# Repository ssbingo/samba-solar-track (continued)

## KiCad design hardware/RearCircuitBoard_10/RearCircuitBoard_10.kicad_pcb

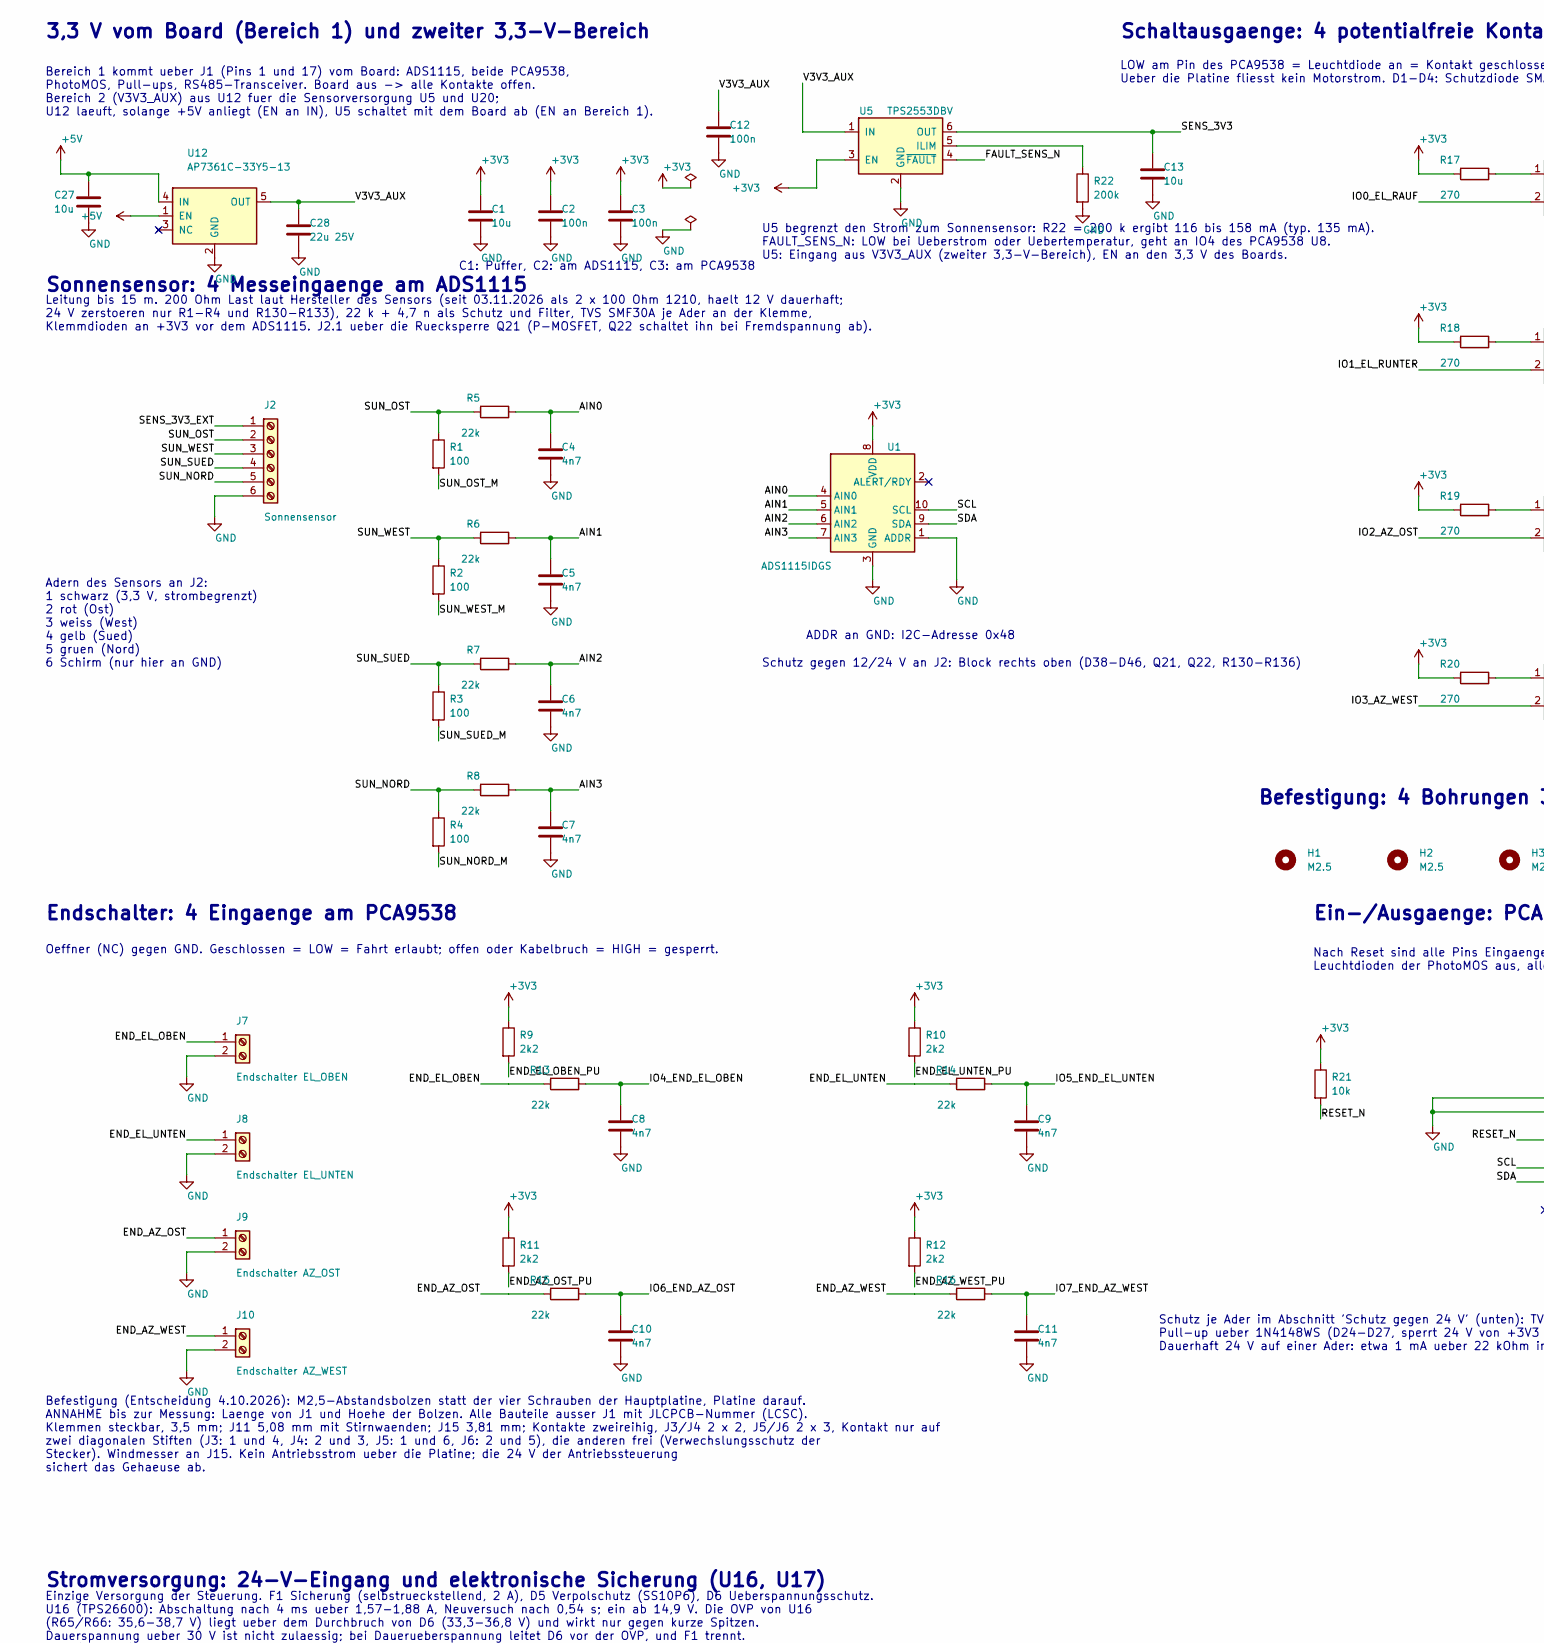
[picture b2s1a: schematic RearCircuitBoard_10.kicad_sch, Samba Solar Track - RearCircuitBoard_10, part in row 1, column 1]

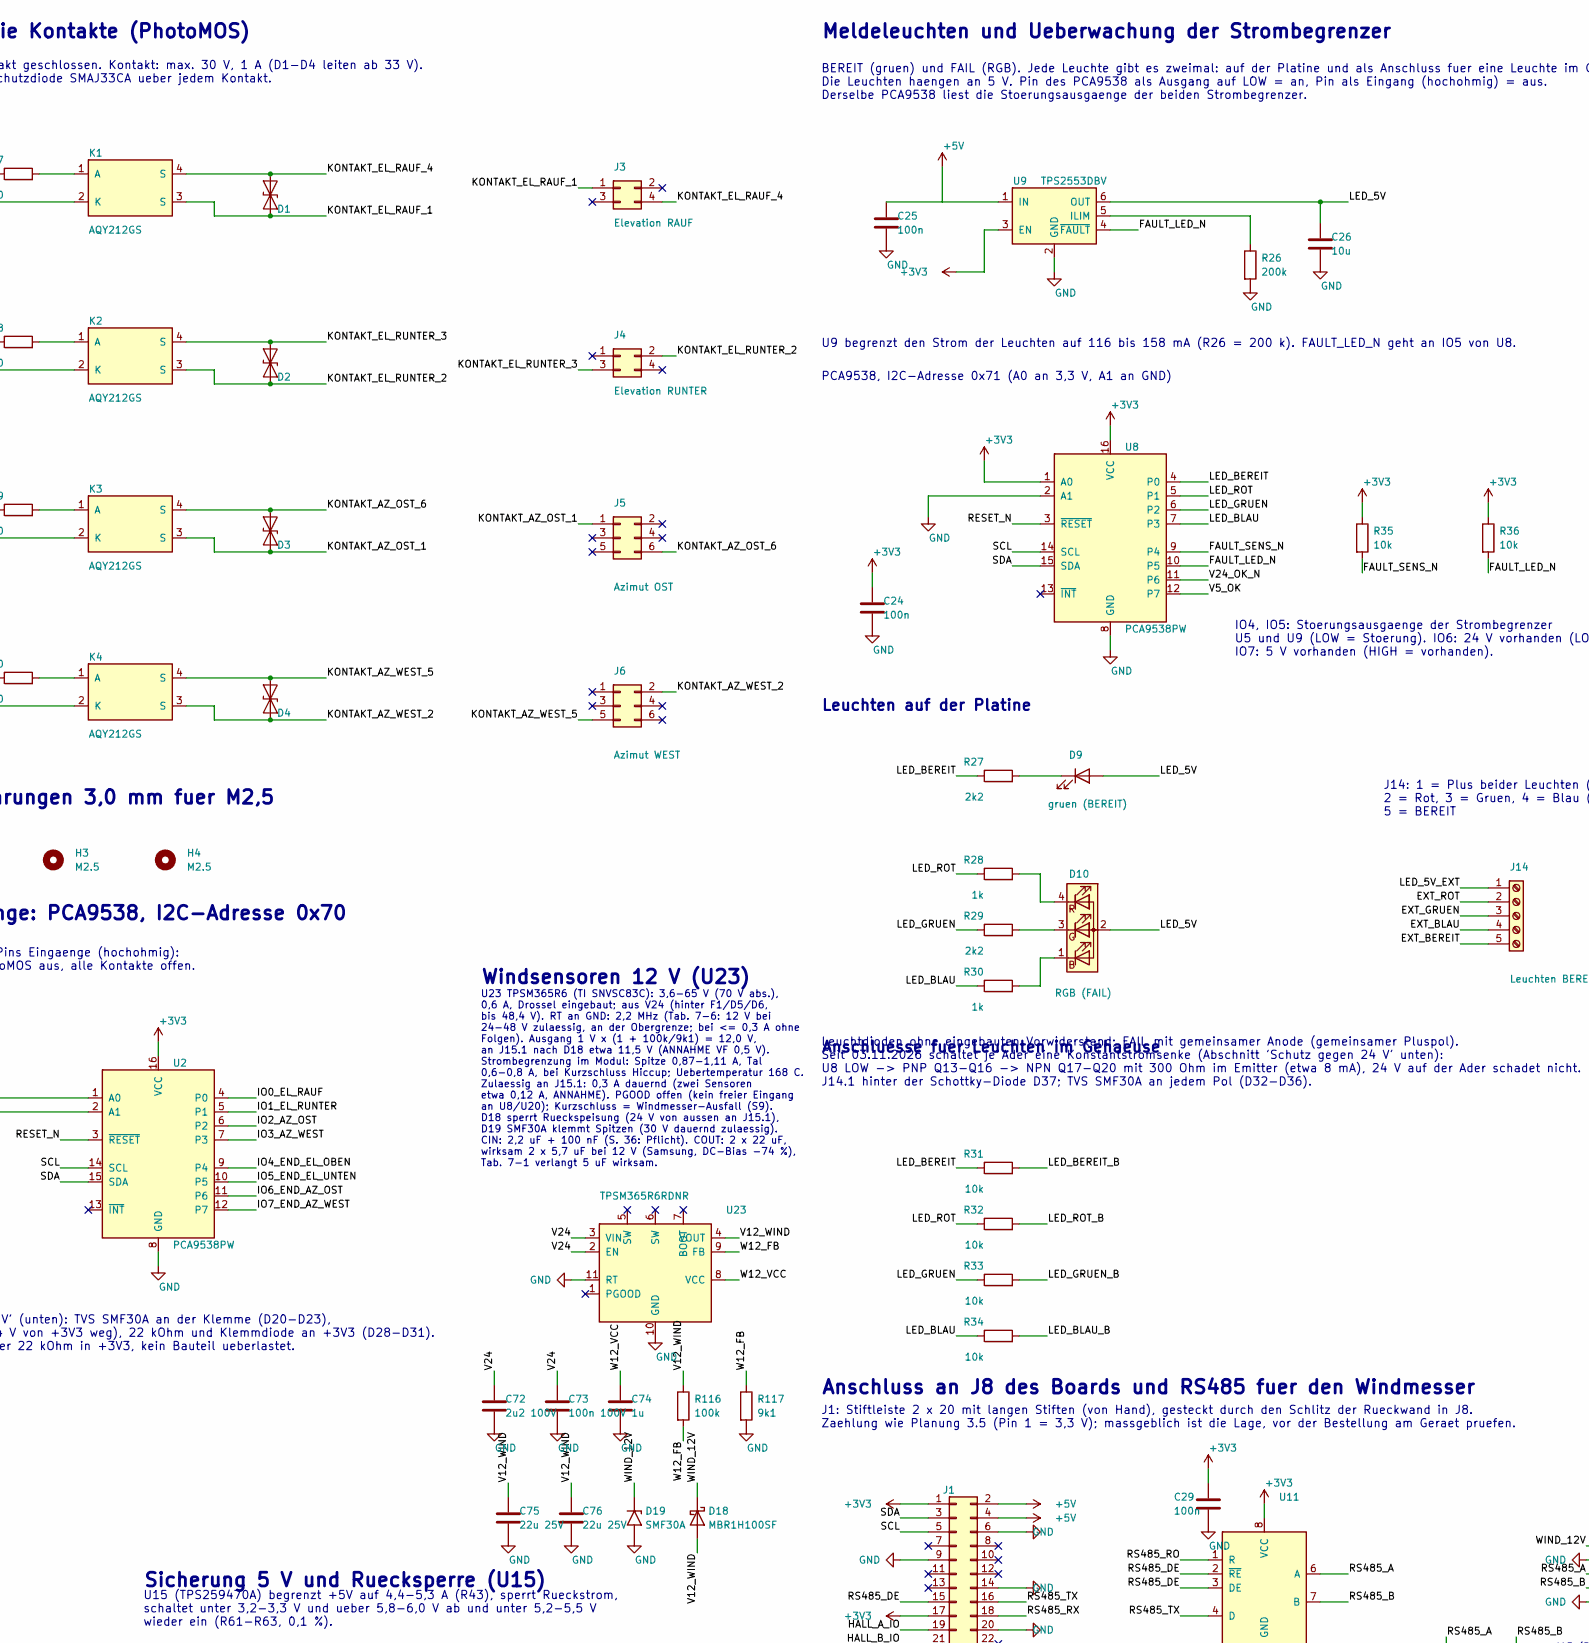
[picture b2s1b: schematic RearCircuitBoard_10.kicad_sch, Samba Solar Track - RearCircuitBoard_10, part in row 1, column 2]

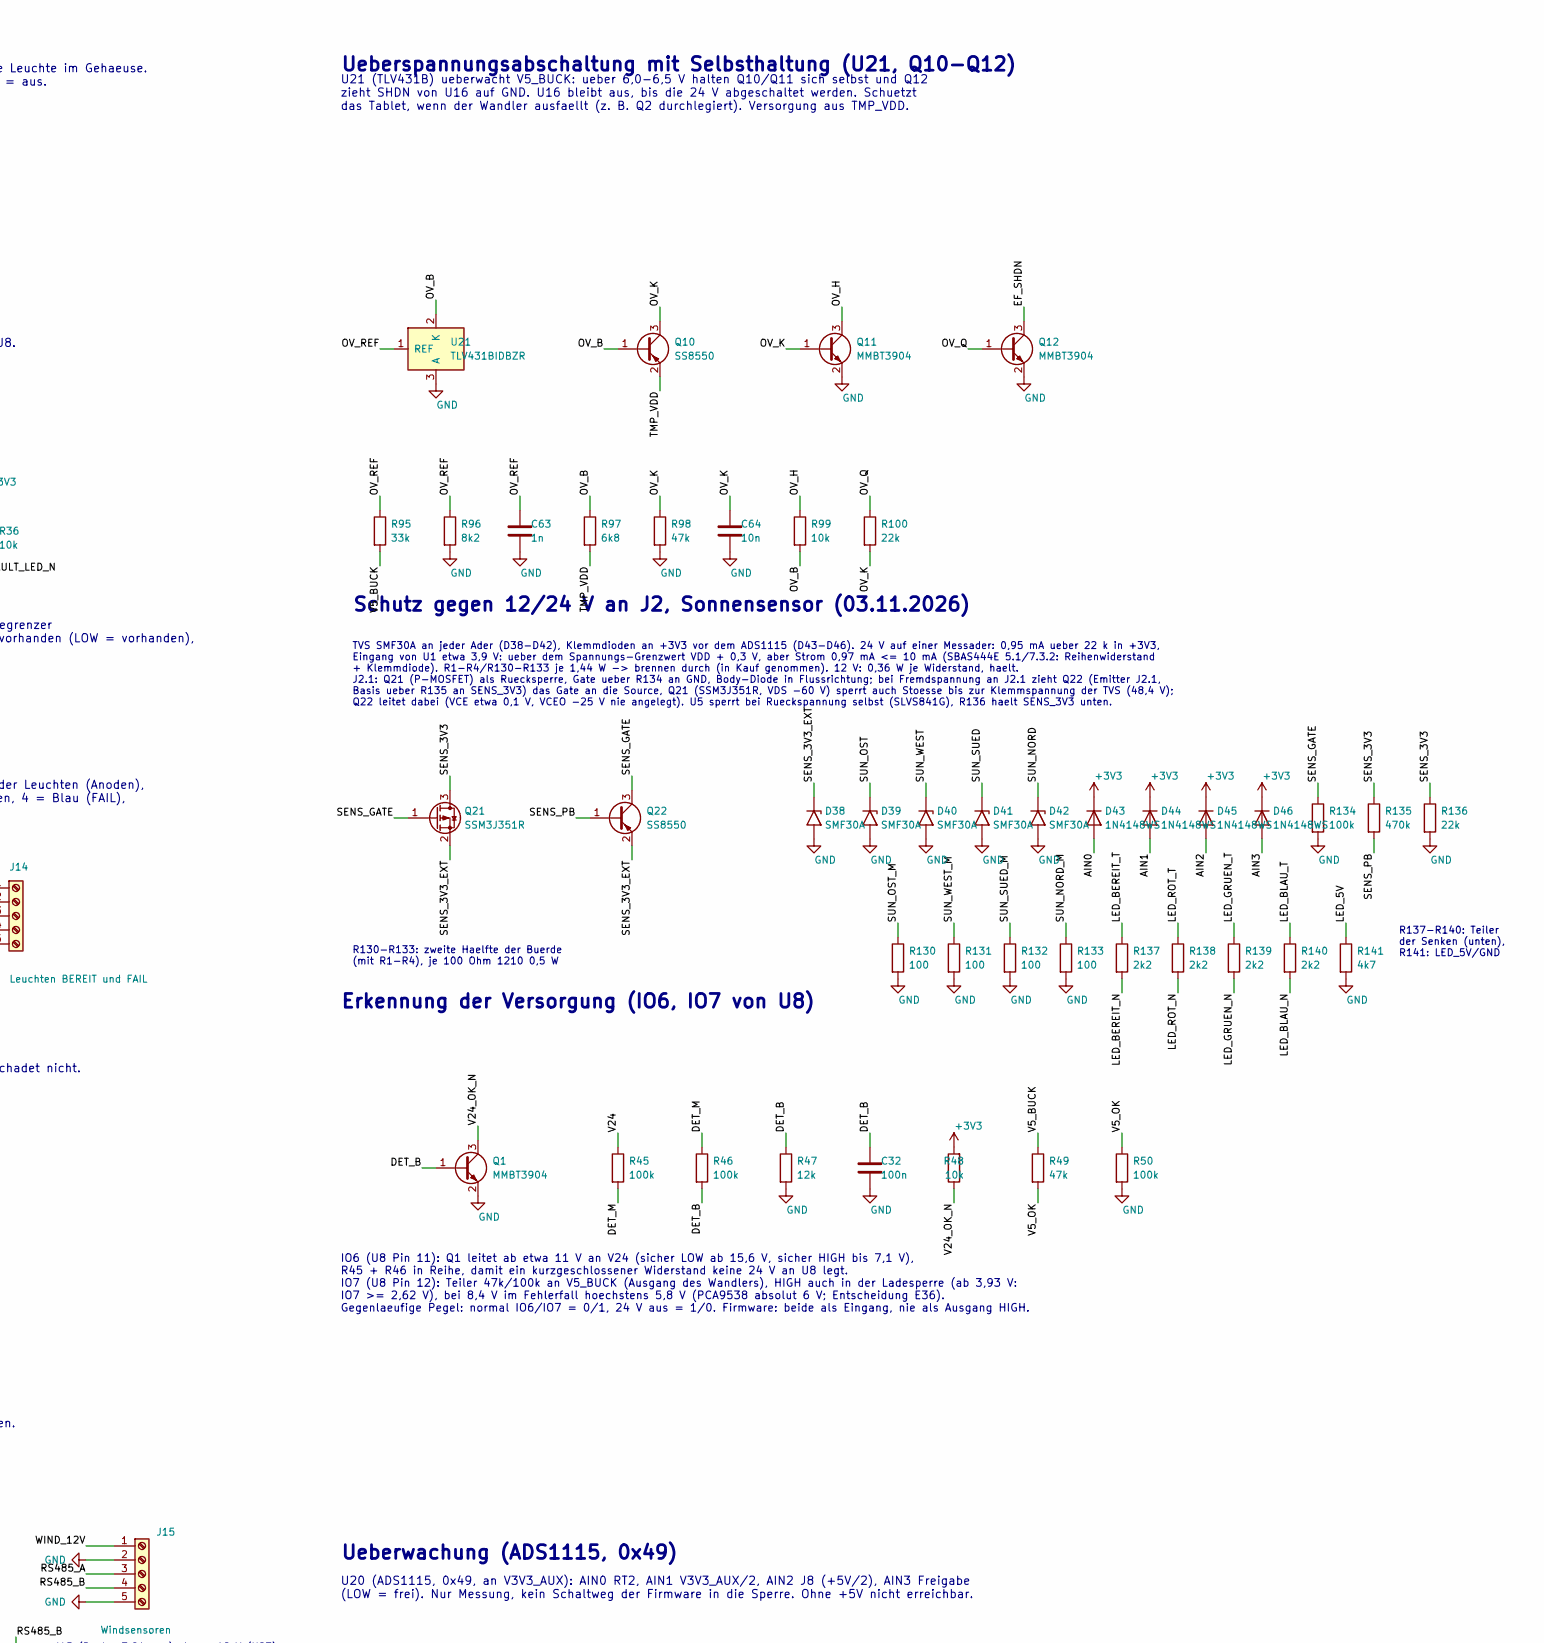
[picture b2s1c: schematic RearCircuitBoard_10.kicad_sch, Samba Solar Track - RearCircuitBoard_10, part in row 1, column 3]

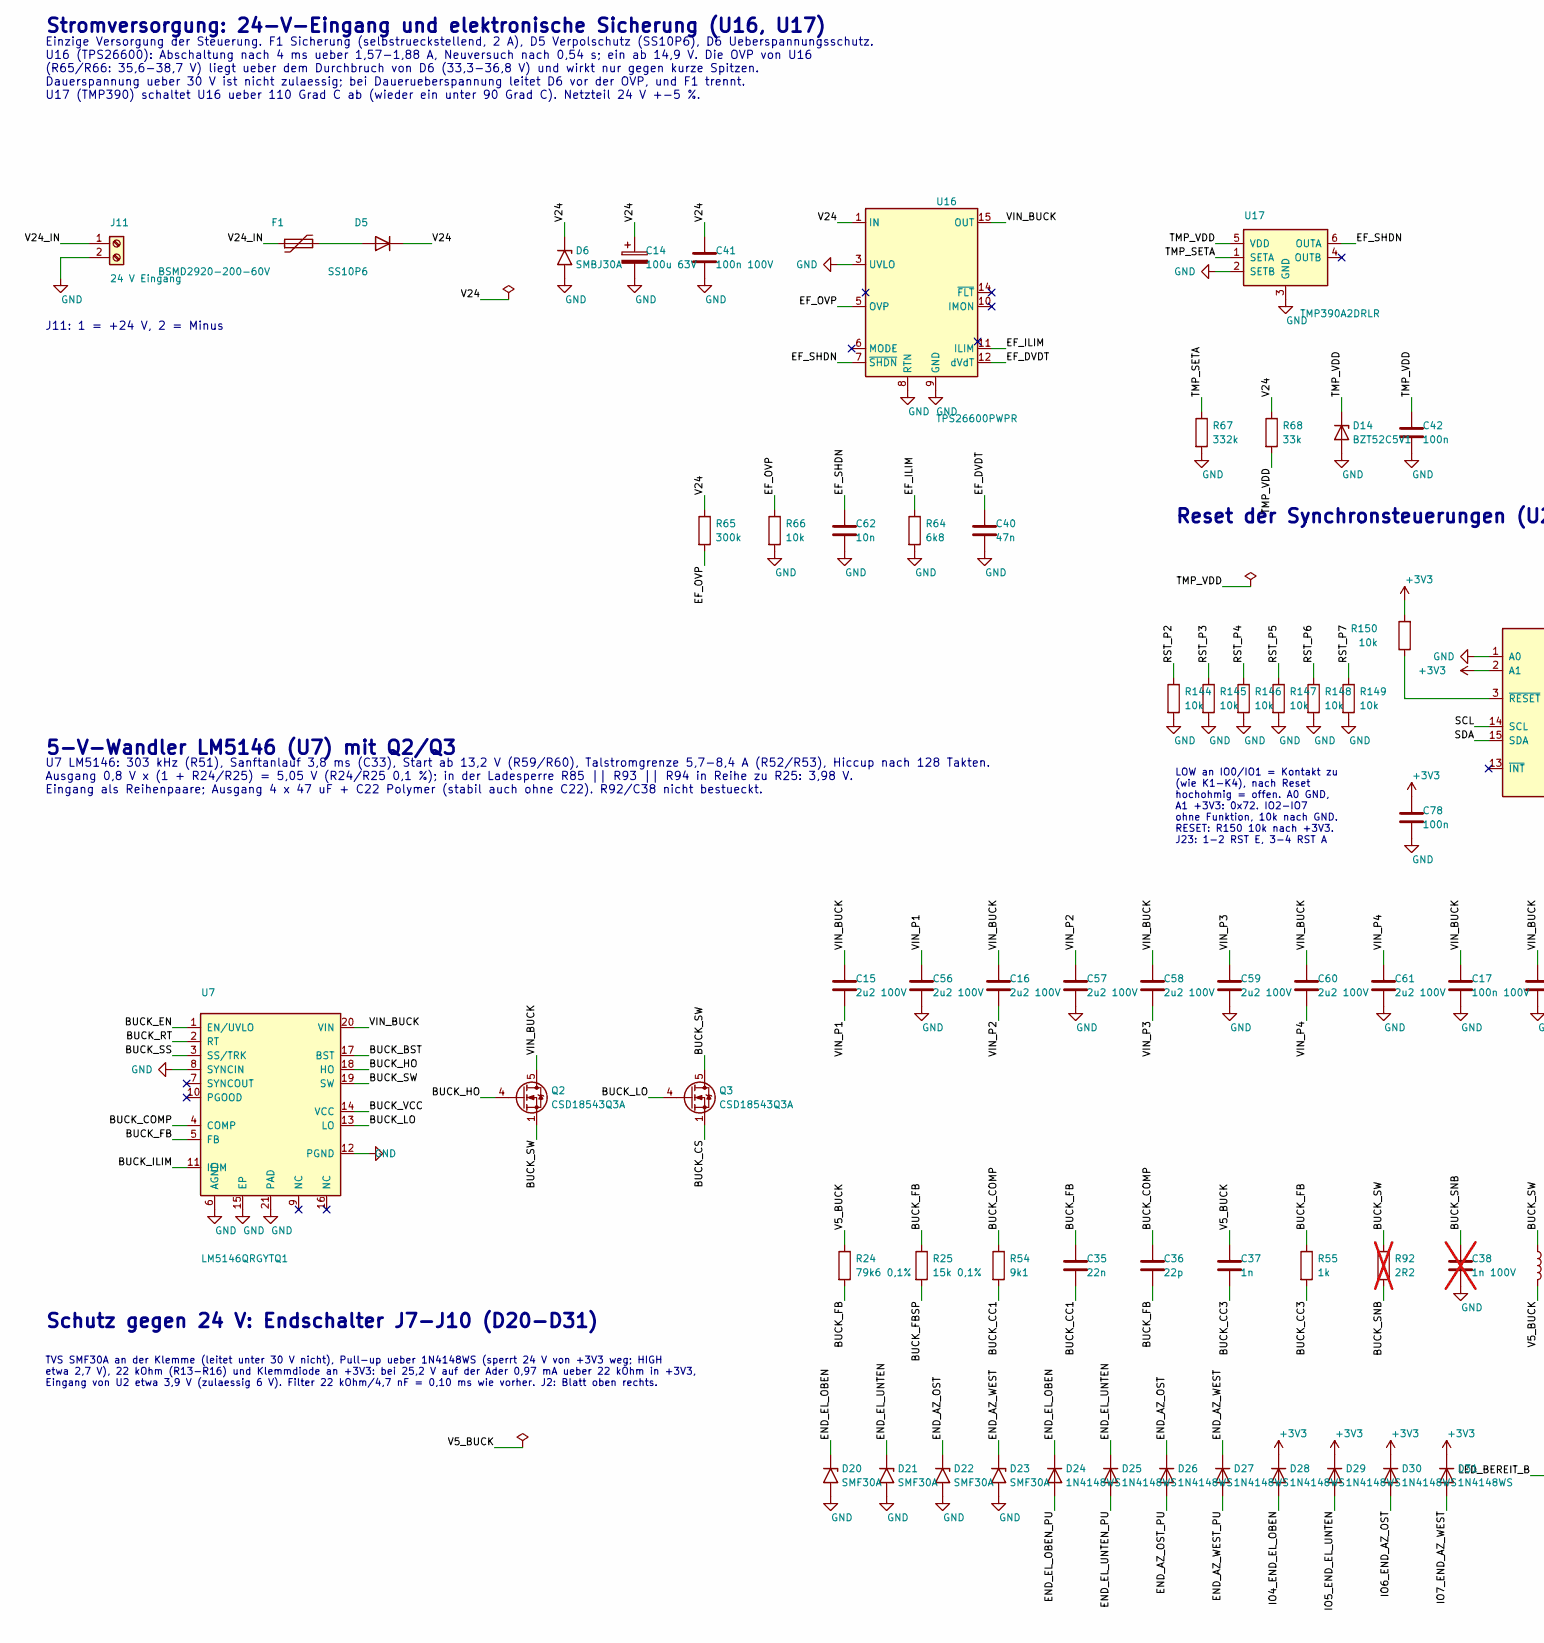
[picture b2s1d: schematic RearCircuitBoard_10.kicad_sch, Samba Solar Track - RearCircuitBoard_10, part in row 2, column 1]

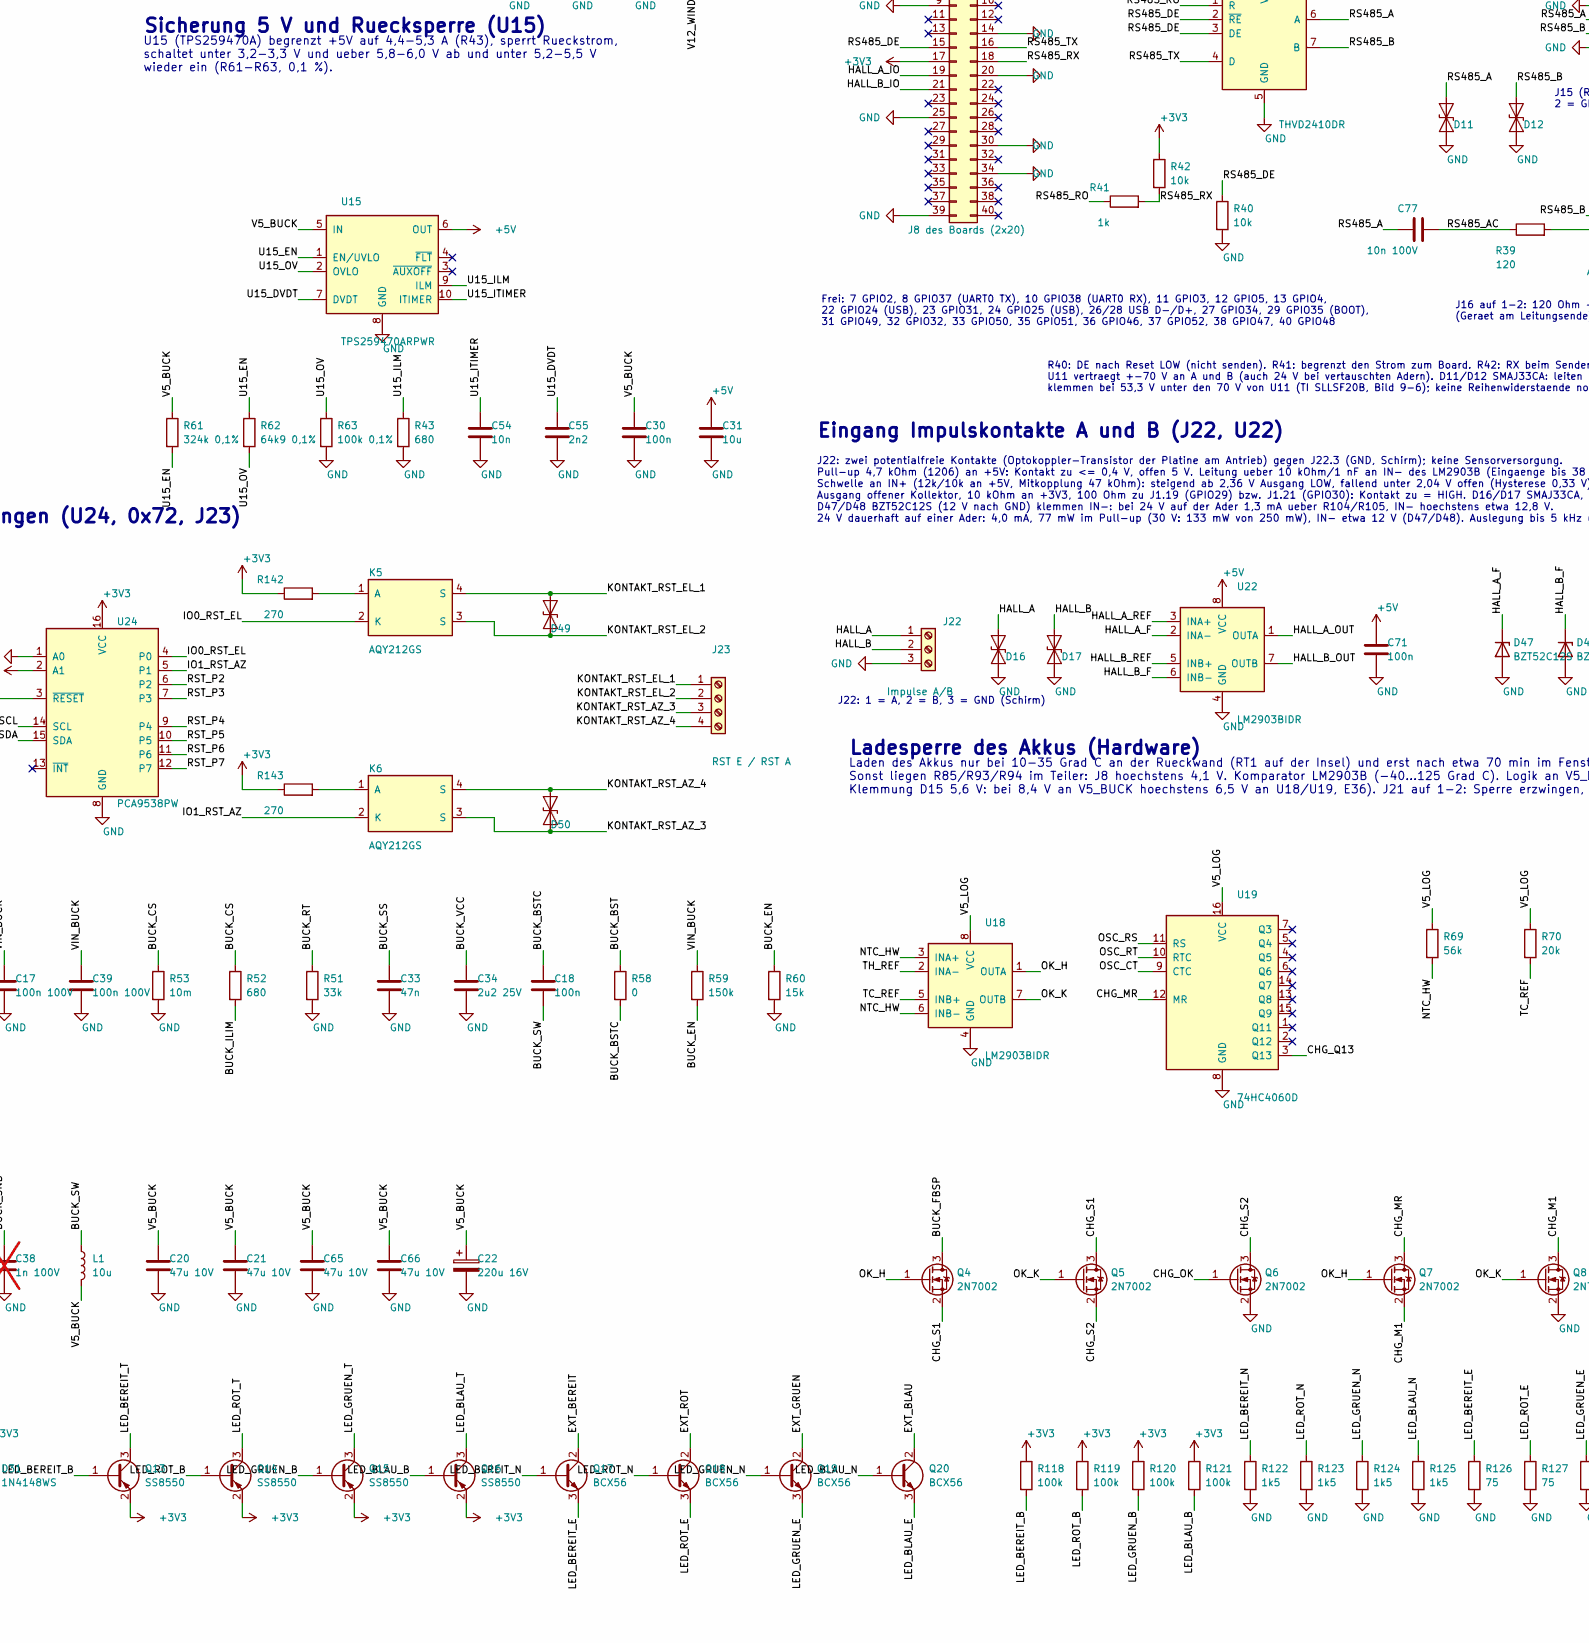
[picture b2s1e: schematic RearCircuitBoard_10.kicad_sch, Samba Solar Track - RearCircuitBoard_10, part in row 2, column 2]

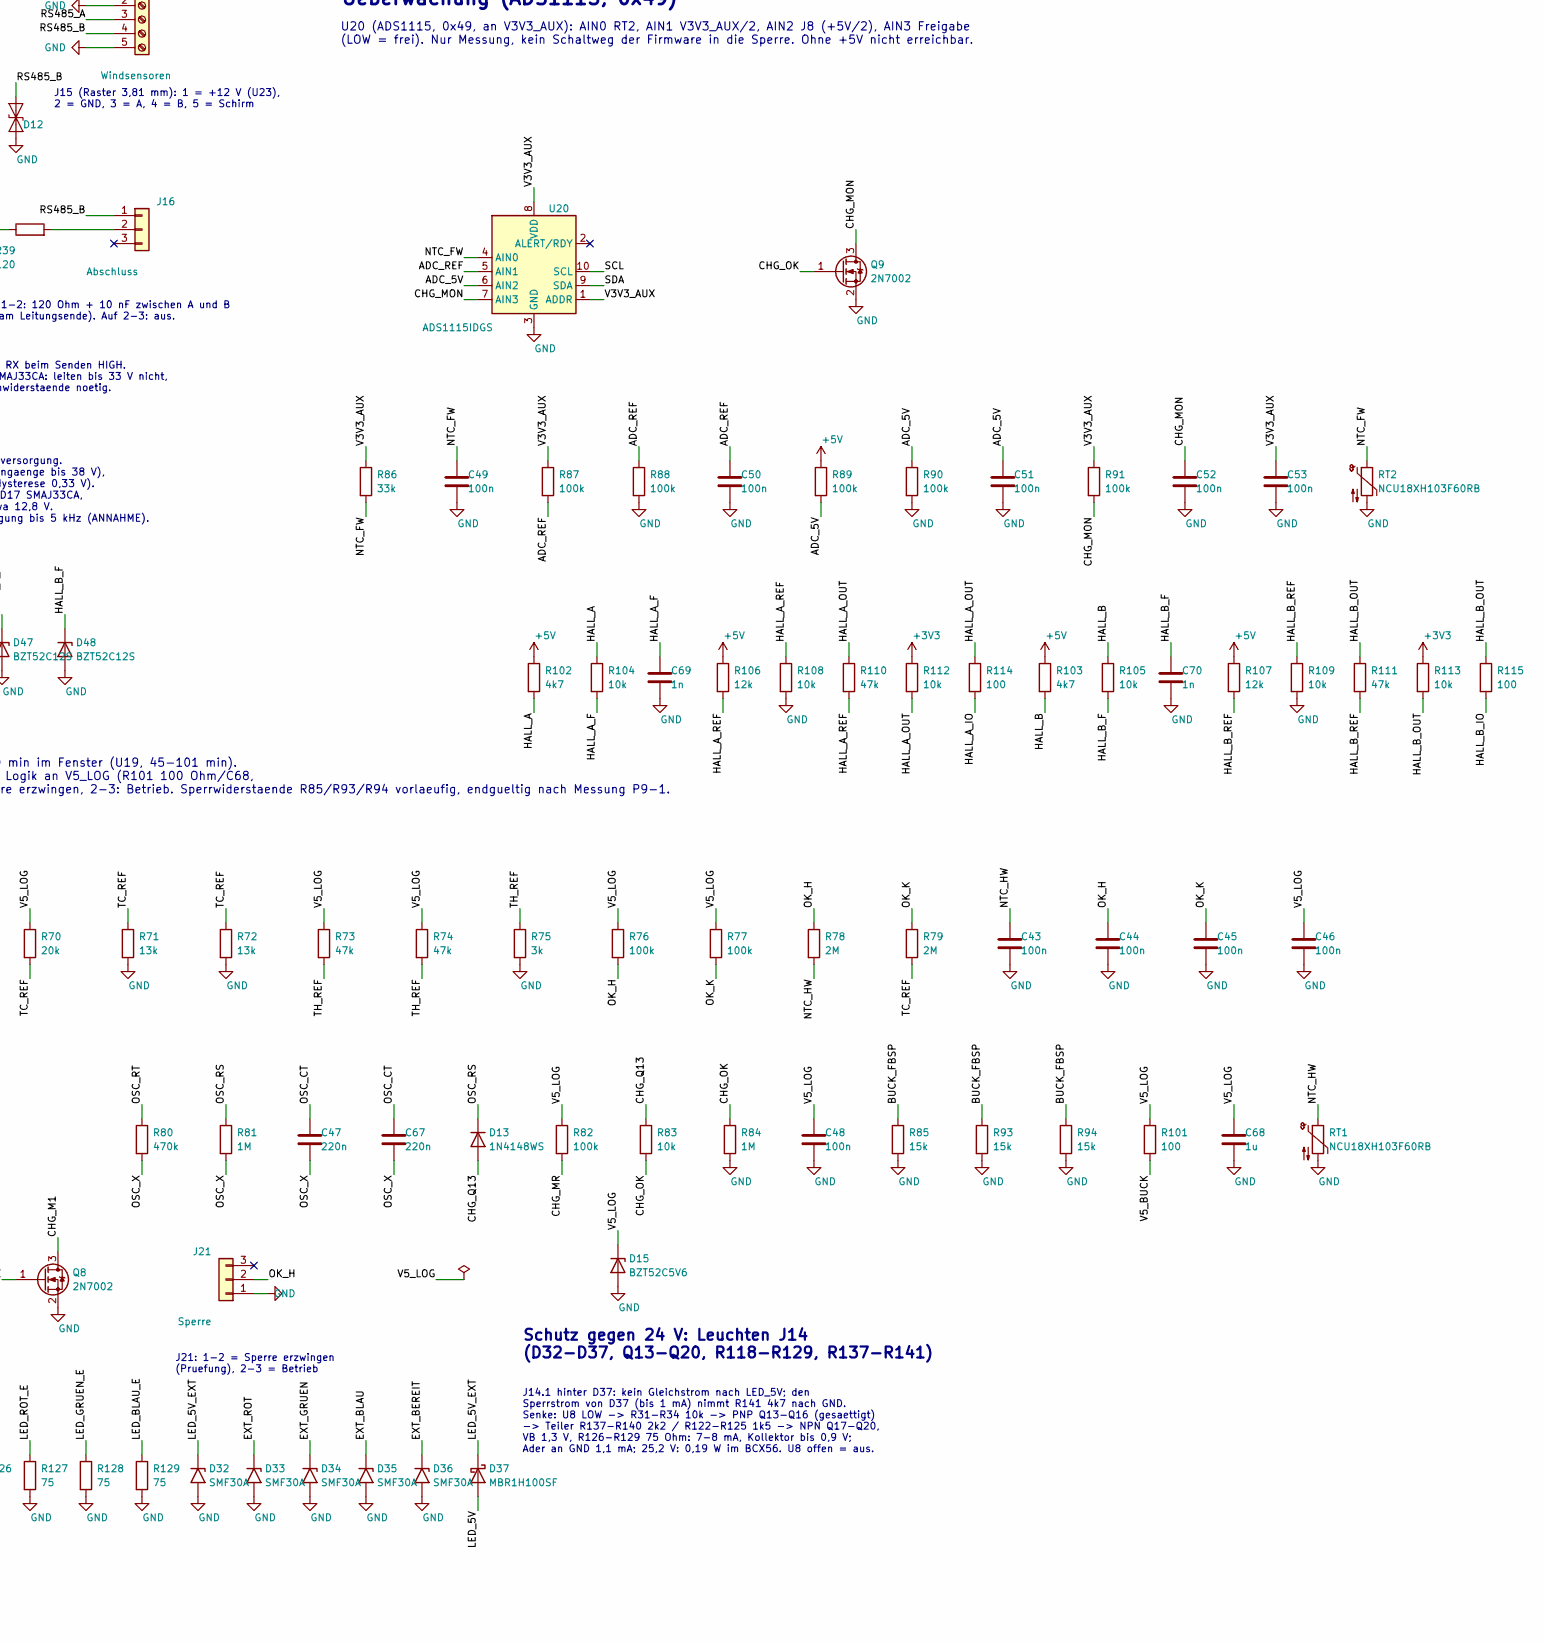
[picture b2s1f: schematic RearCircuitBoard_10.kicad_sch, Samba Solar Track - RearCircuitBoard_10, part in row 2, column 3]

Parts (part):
C1, C13, C26, C27: 10u; C_0603_1608Metric; LCSC C19702
C2, C3, C12, C18, C24, C25, C29, C30, C32, C42, C43, C44, C45, C46, C48, C49, C50, C51, C52, C53, C71, C78: 100n; C_0603_1608Metric; LCSC C14663
C4, C5, C6, C7, C8, C9, C10, C11: 4n7; C_0603_1608Metric; LCSC C53987
C14: 100u 63V; CP_Elec_8x10; LCSC C487384
C15, C16, C56, C57, C58, C59, C60, C61, C72: 2u2 100V; C_1206_3216Metric; LCSC C16195971
C17, C39, C41: 100n 100V; C_0805_2012Metric; LCSC C3011698
C20, C21, C65, C66: 47u 10V; C_1210_3225Metric; LCSC C7198516
C22: 220u 16V; CP_Elec_6.3x7.7; LCSC C709481
C28, C75, C76: 22u 25V; C_1206_3216Metric; LCSC C12891
C31: 10u; C_0603_1608Metric; LCSC C2959727
C33, C40: 47n; C_0603_1608Metric; LCSC C1622
C34: 2u2 25V; C_0805_2012Metric; LCSC C19110
C35: 22n; C_0603_1608Metric; LCSC C21122
C36: 22p; C_0603_1608Metric; LCSC C1653
C37, C63, C69, C70: 1n; C_0603_1608Metric; LCSC C1588
C38: 1n 100V; C_0603_1608Metric; LCSC C43847; not fitted
C47, C67: 220n; C_0603_1608Metric; LCSC C21120
C54, C62, C64: 10n; C_0603_1608Metric; LCSC C57112
C55: 2n2; C_0603_1608Metric; LCSC C1604
C68, C74: 1u; C_0603_1608Metric; LCSC C15849
C73: 100n 100V; C_0402_ohne_Druck; LCSC C3869216
C77: 10n 100V; C_0402_ohne_Druck; LCSC C527014
D1, D2, D3, D4, D11, D12, D16, D17, D49, D50: SMAJ33CA; D_SMA; LCSC C115251
D5: SS10P6; TO-277A; LCSC C2927414
D6: SMBJ30A; D_SMB; LCSC C113998
D9: gruen (BEREIT); LED_0805_2012Metric; LCSC C2297
D10: RGB (FAIL); LED_RGB_PLCC4_S4-3528RGBTA; LCSC C2827321
D13, D24, D25, D26, D27, D28, D29, D30, D31, D43, D44, D45, D46: 1N4148WS; D_SOD-323; LCSC C2128
D14: BZT52C5V1; D_SOD-123; LCSC C173407
D15: BZT52C5V6; D_SOD-123; LCSC C19077402
D18, D37: MBR1H100SF; D_SOD-123F; LCSC C235757
D19, D20, D21, D22, D23, D32, D33, D34, D35, D36, D38, D39, D40, D41, D42: SMF30A; D_SOD-123F; LCSC C364281
D47, D48: BZT52C12S; D_SOD-323; LCSC C19077447
F1: BSMD2920-200-60V; Fuse_2920_7451Metric; LCSC C49233174
H1, H2, H3, H4: M2.5; MountingHole_3mm
J1: J8 des Boards (2x20); PinHeader_2x20_P2.54mm_Unterseite
J2: Sonnensensor; Klemme_3.5_6P_KF2EDGR; LCSC C441175
J3: Elevation RAUF; Klemme_3.5_2x2P_KF2EDGSR; LCSC C2923260
J4: Elevation RUNTER; Klemme_3.5_2x2P_KF2EDGSR; LCSC C2923260
J5: Azimut OST; Klemme_3.5_2x3P_KF2EDGSR; LCSC C2923261
J6: Azimut WEST; Klemme_3.5_2x3P_KF2EDGSR; LCSC C2923261
J7: Endschalter EL_OBEN; Klemme_3.5_2P_KF2EDGR; LCSC C441171
J8: Endschalter EL_UNTEN; Klemme_3.5_2P_KF2EDGR; LCSC C441171
J9: Endschalter AZ_OST; Klemme_3.5_2P_KF2EDGR; LCSC C441171
J10: Endschalter AZ_WEST; Klemme_3.5_2P_KF2EDGR; LCSC C441171
J11: 24 V Eingang; Klemme_5.08_2P_KF2EDGRC; LCSC C441236
J14: Leuchten BEREIT und FAIL; Klemme_3.5_5P_KF2EDGR; LCSC C441174
J15: Windsensoren; Klemme_3.81_5P_KF2EDGR; LCSC C441185
J16: Abschluss; PinHeader_1x03_P2.54mm_Vertical; LCSC C2937625
J21: Sperre; PinHeader_1x03_P2.54mm_Vertical; LCSC C2937625
J22: Impulse A/B; Klemme_3.5_3P_KF2EDGR; LCSC C441172
J23: RST E / RST A; Klemme_3.5_4P_KF2EDGR; LCSC C441173
K1, K2, K3, K4, K5, K6: AQY212GS; SOP-4_4.4x4.3mm_P2.54mm_Panasonic; LCSC C415471
L1: 10u; L_Wuerth_WE-LHMI_1040; LCSC C1519857
Q1, Q11, Q12: MMBT3904; SOT-23; LCSC C20526
Q2, Q3: CSD18543Q3A; TI_DNH0008A_CSD18543Q3A; LCSC C840100
Q4, Q5, Q6, Q7, Q8, Q9: 2N7002; SOT-23; LCSC C8545
Q10, Q13, Q14, Q15, Q16, Q22: SS8550; SOT-23; LCSC C8542
Q17, Q18, Q19, Q20: BCX56; SOT-89-3; LCSC C24280
Q21: SSM3J351R; SOT-23; LCSC C150147
R1, R2, R3, R4, R130, R131, R132, R133: 100; R_1210_3225Metric; LCSC C620661
R5, R6, R7, R8, R13, R14, R15, R16, R100, R136: 22k; R_0603_1608Metric; LCSC C31850
R9, R10, R11, R12, R27, R29, R137, R138, R139, R140: 2k2; R_0603_1608Metric; LCSC C4190
R17, R18, R19, R20, R142, R143: 270; R_0603_1608Metric; LCSC C22966
R21, R31, R32, R33, R34, R35, R36, R40, R42, R48, R66, R83, R99, R104, R105, R108, R109, R112, R113, R144, R145, R146, R147, R148, R149, R150: 10k; R_0603_1608Metric; LCSC C25804
R22, R26: 200k; R_0603_1608Metric; LCSC C25811
R24: 79k6 0,1%; R_0603_1608Metric; LCSC C861560
R25: 15k 0,1%; R_0603_1608Metric; LCSC C326733
R28, R30, R41, R55: 1k; R_0603_1608Metric; LCSC C21190
R39: 120; R_0805_2012Metric; LCSC C17437
R43, R52: 680; R_0603_1608Metric; LCSC C23228
R45, R46, R50, R76, R77, R82, R87, R88, R89, R90, R91, R116, R118, R119, R120, R121, R134: 100k; R_0603_1608Metric; LCSC C25803
R47, R106, R107: 12k; R_0603_1608Metric; LCSC C22790
R49, R73, R74, R98, R110, R111: 47k; R_0603_1608Metric; LCSC C25819
R51, R68, R86, R95: 33k; R_0603_1608Metric; LCSC C4216
R53: 10m; R_1206_3216Metric; LCSC C2076185
R54, R117: 9k1; R_0603_1608Metric; LCSC C23260
R58: 0; R_0603_1608Metric; LCSC C21189
R59: 150k; R_0603_1608Metric; LCSC C22807
R60, R85, R93, R94: 15k; R_0603_1608Metric; LCSC C22809
R61: 324k 0,1%; R_0603_1608Metric; LCSC C3999394
R62: 64k9 0,1%; R_0603_1608Metric; LCSC C861510
R63: 100k 0,1%; R_0603_1608Metric; LCSC C122538
R64, R97: 6k8; R_0603_1608Metric; LCSC C23212
R65: 300k; R_0603_1608Metric; LCSC C23024
R67: 332k; R_0603_1608Metric; LCSC C23139
R69: 56k; R_0603_1608Metric; LCSC C23206
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
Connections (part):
+3V3: C1.1, C2.1, C3.1, C24.1, C29.1, C78.1, D28.1 (K), D29.1 (K), D30.1 (K), D31.1 (K), D43.1 (K), D44.1 (K), D45.1 (K), D46.1 (K), J1.1, J1.17, Q13.2 (E), Q14.2 (E), Q15.2 (E), Q16.2 (E), R9.1, R10.1, R11.1, R12.1, R17.1, R18.1, R19.1, R20.1, R21.1, R35.1, R36.1, R42.1, R48.2, R112.1, R113.1, R118.1, R119.1, R120.1, R121.1, R142.1, R143.1, R150.2, U1.8 (VDD), U2.16 (VCC), U5.3 (EN), U8.1 (A0), U8.16 (VCC), U9.3 (EN), U11.8 (VCC), U24.2 (A1), U24.16 (VCC)
+5V: C25.1, C27.1, C31.1, C71.1, J1.2, J1.4, R89.1, R102.1, R103.1, R106.1, R107.1, U9.1 (IN), U12.1 (EN), U12.4 (IN), U15.6 (OUT), U22.8 (VCC)
/ADC_5V: C51.1, R89.2, R90.1, U20.6 (AIN2)
/ADC_REF: C50.1, R87.2, R88.1, U20.5 (AIN1)
/AIN0: C4.1, D43.2 (A), R5.2, U1.4 (AIN0)
/AIN1: C5.1, D44.2 (A), R6.2, U1.5 (AIN1)
/AIN2: C6.1, D45.2 (A), R7.2, U1.6 (AIN2)
/AIN3: C7.1, D46.2 (A), R8.2, U1.7 (AIN3)
/BUCK_BST: R58.1, U7.17 (BST)
/BUCK_BSTC: C18.1, R58.2
/BUCK_CC1: C35.2, R54.2
/BUCK_CC3: C37.2, R55.2
/BUCK_COMP: C36.1, R54.1, U7.4 (COMP)
/BUCK_CS: Q3.1 (S), Q3.2 (S), Q3.3 (S), R52.1, R53.1
/BUCK_EN: R59.2, R60.1, U7.1 (EN/UVLO)
/BUCK_FB: C35.1, C36.2, R24.2, R25.1, R55.1, U7.5 (FB)
/BUCK_FBSP: Q4.3 (D), R25.2, R85.1, R93.1, R94.1
/BUCK_HO: Q2.4 (G), U7.18 (HO)
/BUCK_ILIM: R52.2, U7.11 (ILIM)
/BUCK_LO: Q3.4 (G), U7.13 (LO)
/BUCK_RT: R51.1, U7.2 (RT)
/BUCK_SNB: C38.1, R92.2
/BUCK_SS: C33.1, U7.3 (SS/TRK)
/BUCK_SW: C18.2, L1.1, Q2.1 (S), Q2.2 (S), Q2.3 (S), Q3.5 (D), R92.1, U7.19 (SW)
/BUCK_VCC: C34.1, U7.14 (VCC)
/CHG_M1: Q7.2 (S), Q8.3 (D)
/CHG_MON: C52.1, Q9.3 (D), R91.2, U20.7 (AIN3)
/CHG_MR: Q7.3 (D), R82.2, U19.12 (MR)
/CHG_OK: Q6.1 (G), Q9.1 (G), R83.2, R84.1
/CHG_Q13: D13.2 (A), R83.1, U19.3 (Q13)
/CHG_S1: Q4.2 (S), Q5.3 (D)
/CHG_S2: Q5.2 (S), Q6.3 (D)
/DET_B: C32.1, Q1.1 (B), R46.2, R47.1
/DET_M: R45.2, R46.1
/EF_DVDT: C40.1, U16.12 (dVdT)
/EF_ILIM: R64.1, U16.11 (ILIM)
/EF_OVP: R65.2, R66.1, U16.5 (OVP)
/EF_SHDN: C62.1, Q12.3 (C), U16.7 (~SHDN), U17.6 (OUTA)
/END_AZ_OST: D22.1 (A1), D26.1 (K), J9.1, R15.1
/END_AZ_OST_PU: D26.2 (A), R11.2
/END_AZ_WEST: D23.1 (A1), D27.1 (K), J10.1, R16.1
/END_AZ_WEST_PU: D27.2 (A), R12.2
/END_EL_OBEN: D20.1 (A1), D24.1 (K), J7.1, R13.1
/END_EL_OBEN_PU: D24.2 (A), R9.2
/END_EL_UNTEN: D21.1 (A1), D25.1 (K), J8.1, R14.1
/END_EL_UNTEN_PU: D25.2 (A), R10.2
/EXT_BEREIT: D36.1 (A1), J14.5, Q17.2 (C)
/EXT_BLAU: D35.1 (A1), J14.4, Q20.2 (C)
/EXT_GRUEN: D34.1 (A1), J14.3, Q19.2 (C)
/EXT_ROT: D33.1 (A1), J14.2, Q18.2 (C)
/FAULT_LED_N: R36.2, U8.10 (P5), U9.4 (~FAULT)
/FAULT_SENS_N: R35.2, U5.4 (~FAULT), U8.9 (P4)
/HALL_A: D16.2 (A2), J22.1, R102.2, R104.1
/HALL_A_F: C69.1, D47.1 (K), R104.2, U22.2 (INA-)
/HALL_A_IO: J1.19, R114.2
/HALL_A_OUT: R110.1, R112.2, R114.1, U22.1 (OUTA)
/HALL_A_REF: R106.2, R108.1, R110.2, U22.3 (INA+)
/HALL_B: D17.2 (A2), J22.2, R103.2, R105.1
/HALL_B_F: C70.1, D48.1 (K), R105.2, U22.6 (INB-)
/HALL_B_IO: J1.21, R115.2
/HALL_B_OUT: R111.1, R113.2, R115.1, U22.7 (OUTB)
/HALL_B_REF: R107.2, R109.1, R111.2, U22.5 (INB+)
/IO0_EL_RAUF: K1.2 (K), U2.4 (P0)
/IO0_RST_EL: K5.2 (K), U24.4 (P0)
/IO1_EL_RUNTER: K2.2 (K), U2.5 (P1)
/IO1_RST_AZ: K6.2 (K), U24.5 (P1)
/IO2_AZ_OST: K3.2 (K), U2.6 (P2)
/IO3_AZ_WEST: K4.2 (K), U2.7 (P3)
/IO4_END_EL_OBEN: C8.1, D28.2 (A), R13.2, U2.9 (P4)
/IO5_END_EL_UNTEN: C9.1, D29.2 (A), R14.2, U2.10 (P5)
/IO6_END_AZ_OST: C10.1, D30.2 (A), R15.2, U2.11 (P6)
/IO7_END_AZ_WEST: C11.1, D31.2 (A), R16.2, U2.12 (P7)
/KONTAKT_AZ_OST_1: D3.1 (A1), J5.1, K3.3 (S)
/KONTAKT_AZ_OST_6: D3.2 (A2), J5.6, K3.4 (S)
/KONTAKT_AZ_WEST_2: D4.1 (A1), J6.2, K4.3 (S)
/KONTAKT_AZ_WEST_5: D4.2 (A2), J6.5, K4.4 (S)
/KONTAKT_EL_RAUF_1: D1.1 (A1), J3.1, K1.3 (S)
/KONTAKT_EL_RAUF_4: D1.2 (A2), J3.4, K1.4 (S)
/KONTAKT_EL_RUNTER_2: D2.1 (A1), J4.2, K2.3 (S)
/KONTAKT_EL_RUNTER_3: D2.2 (A2), J4.3, K2.4 (S)
/KONTAKT_RST_AZ_3: D50.1 (A1), J23.3, K6.3 (S)
/KONTAKT_RST_AZ_4: D50.2 (A2), J23.4, K6.4 (S)
/KONTAKT_RST_EL_1: D49.2 (A2), J23.1, K5.4 (S)
/KONTAKT_RST_EL_2: D49.1 (A1), J23.2, K5.3 (S)
/LED_5V: C26.1, D9.2 (A), D10.2 (A), D37.2 (A), R141.1, U9.6 (OUT)
/LED_5V_EXT: D32.1 (A1), D37.1 (K), J14.1
/LED_BEREIT: R27.1, R31.1, U8.4 (P0)
/LED_BEREIT_B: Q13.1 (B), R31.2, R118.2
/LED_BEREIT_E: Q17.3 (E), R126.1
/LED_BEREIT_N: Q17.1 (B), R122.1, R137.2
/LED_BEREIT_T: Q13.3 (C), R137.1
/LED_BLAU: R30.1, R34.1, U8.7 (P3)
/LED_BLAU_B: Q16.1 (B), R34.2, R121.2
/LED_BLAU_E: Q20.3 (E), R129.1
/LED_BLAU_N: Q20.1 (B), R125.1, R140.2
/LED_BLAU_T: Q16.3 (C), R140.1
/LED_GRUEN: R29.1, R33.1, U8.6 (P2)
/LED_GRUEN_B: Q15.1 (B), R33.2, R120.2
/LED_GRUEN_E: Q19.3 (E), R128.1
/LED_GRUEN_N: Q19.1 (B), R124.1, R139.2
/LED_GRUEN_T: Q15.3 (C), R139.1
/LED_ROT: R28.1, R32.1, U8.5 (P1)
/LED_ROT_B: Q14.1 (B), R32.2, R119.2
/LED_ROT_E: Q18.3 (E), R127.1
/LED_ROT_N: Q18.1 (B), R123.1, R138.2
/LED_ROT_T: Q14.3 (C), R138.1
/NTC_FW: C49.1, R86.2, RT2.1, U20.4 (AIN0)
/NTC_HW: C43.1, R69.2, R78.2, RT1.1, U18.3 (INA+), U18.6 (INB-)
/OK_H: C44.1, J21.2, Q4.1 (G), Q7.1 (G), R76.2, R78.1, U18.1 (OUTA)
/OK_K: C45.1, Q5.1 (G), Q8.1 (G), R77.2, R79.1, U18.7 (OUTB)
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
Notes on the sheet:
3,3 V vom Board (Bereich 1) und zweiter 3,3-V-Bereich
Bereich 1 kommt ueber J1 (Pins 1 und 17) vom Board: ADS1115, beide PCA9538, PhotoMOS, Pull-ups, RS485-Transceiver. Board aus -> alle Kontakte offen. Bereich 2 (V3V3_AUX) aus U12 fuer die Sensorversorgung U5 und U20; U12 laeuft, solange +5V anliegt (EN an IN), U5 schaltet mit dem Board ab (EN an Ber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
C1: Puffer, C2: am ADS1115, C3: am PCA9538
U5 begrenzt den Strom zum Sonnensensor: R22 = 200 k ergibt 116 bis 158 mA (typ. 135 mA). FAULT_SENS_N: LOW bei Ueberstrom oder Uebertemperatur, geht an IO4 des PCA9538 U8. U5: Eingang aus V3V3_AUX (zweiter 3,3-V-Bereich), EN an den 3,3 V des Boards.
Sonnensensor: 4 Messeingaenge am ADS1115
Leitung bis 15 m. 200 Ohm Last laut Hersteller des Sensors (seit 03.11.2026 als 2 x 100 Ohm 1210, haelt 12 V dauerhaft; 24 V zerstoeren nur R1-R4 und R130-R133), 22 k + 4,7 n als Schutz und Filter, TVS SMF30A je Ader an der Klemme, Klemmdioden an +3V3 vor dem ADS1115. J2.1 ueber die Ruecksperre Q21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
Adern des Sensors an J2: 1 schwarz (3,3 V, strombegrenzt) 2 rot (Ost) 3 weiss (West) 4 gelb (Sued) 5 gruen (Nord) 6 Schirm (nur hier an GND)
ADDR an GND: I2C-Adresse 0x48
Schutz gegen 12/24 V an J2: Block rechts oben (D38-D46, Q21, Q22, R130-R136)
Schutz gegen 12/24 V an J2, Sonnensensor (03.11.2026)
TVS SMF30A an jeder Ader (D38-D42), Klemmdioden an +3V3 vor dem ADS1115 (D43-D46). 24 V auf einer Messader: 0,95 mA ueber 22 k in +3V3, Eingang von U1 etwa 3,9 V: ueber dem Spannungs-Grenzwert VDD + 0,3 V, aber Strom 0,97 mA <= 10 mA (SBAS444E 5.1/7.3.2: Reihenwiderstand + Klemmdiode). R1-R4/R130-R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
R130-R133: zweite Haelfte der Buerde (mit R1-R4), je 100 Ohm 1210 0,5 W
R137-R140: Teiler der Senken (unten), R141: LED_5V/GND
Endschalter: 4 Eingaenge am PCA9538
Oeffner (NC) gegen GND. Geschlossen = LOW = Fahrt erlaubt; offen oder Kabelbruch = HIGH = gesperrt.
Schutz je Ader im Abschnitt 'Schutz gegen 24 V' (unten): TVS SMF30A an der Klemme (D20-D23), Pull-up ueber 1N4148WS (D24-D27, sperrt 24 V von +3V3 weg), 22 kOhm und Klemmdiode an +3V3 (D28-D31). Dauerhaft 24 V auf einer Ader: etwa 1 mA ueber 22 kOhm in +3V3, kein Bauteil ueberlastet.
Ein-/Ausgaenge: PCA9538, I2C-Adresse 0x70
Nach Reset sind alle Pins Eingaenge (hochohmig): Leuchtdioden der PhotoMOS aus, alle Kontakte offen.
Schaltausgaenge: 4 potentialfreie Kontakte (PhotoMOS)
LOW am Pin des PCA9538 = Leuchtdiode an = Kontakt geschlossen. Kontakt: max. 30 V, 1 A (D1-D4 leiten ab 33 V). Ueber die Platine fliesst kein Motorstrom. D1-D4: Schutzdiode SMAJ33CA ueber jedem Kontakt.
Befestigung: 4 Bohrungen 3,0 mm fuer M2,5
Befestigung (Entscheidung 4.10.2026): M2,5-Abstandsbolzen statt der vier Schrauben der Hauptplatine, Platine darauf. ANNAHME bis zur Messung: Laenge von J1 und Hoehe der Bolzen. Alle Bauteile ausser J1 mit JLCPCB-Nummer (LCSC). Klemmen steckbar, 3,5 mm; J11 5,08 mm mit Stirnwaenden; J15 3,81 mm; Ko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
Stromversorgung: 24-V-Eingang und elektronische Sicherung (U16, U17)
Einzige Versorgung der Steuerung. F1 Sicherung (selbstrueckstellend, 2 A), D5 Verpolschutz (SS10P6), D6 Ueberspannungsschutz. U16 (TPS26600): Abschaltung nach 4 ms ueber 1,57-1,88 A, Neuversuch nach 0,54 s; ein ab 14,9 V. Die OVP von U16 (R65/R66: 35,6-38,7 V) liegt ueber dem Durchbruch von D6 (33,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
J11: 1 = +24 V, 2 = Minus
Sicherung 5 V und Ruecksperre (U15)
U15 (TPS259470A) begrenzt +5V auf 4,4-5,3 A (R43), sperrt Rueckstrom, schaltet unter 3,2-3,3 V und ueber 5,8-6,0 V ab und unter 5,2-5,5 V wieder ein (R61-R63, 0,1 %).
5-V-Wandler LM5146 (U7) mit Q2/Q3
U7 LM5146: 303 kHz (R51), Sanftanlauf 3,8 ms (C33), Start ab 13,2 V (R59/R60), Talstromgrenze 5,7-8,4 A (R52/R53), Hiccup nach 128 Takten. Ausgang 0,8 V x (1 + R24/R25) = 5,05 V (R24/R25 0,1 %); in der Ladesperre R85 || R93 || R94 in Reihe zu R25: 3,98 V. Eingang als Reihenpaare; Ausgang 4 x 47 uF 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
Meldeleuchten und Ueberwachung der Strombegrenzer
BEREIT (gruen) und FAIL (RGB). Jede Leuchte gibt es zweimal: auf der Platine und als Anschluss fuer eine Leuchte im Gehaeuse. Die Leuchten haengen an 5 V. Pin des PCA9538 als Ausgang auf LOW = an, Pin als Eingang (hochohmig) = aus. Derselbe PCA9538 liest die Stoerungsausgaenge der beiden Strombegre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
U9 begrenzt den Strom der Leuchten auf 116 bis 158 mA (R26 = 200 k). FAULT_LED_N geht an IO5 von U8.
PCA9538, I2C-Adresse 0x71 (A0 an 3,3 V, A1 an GND)
IO4, IO5: Stoerungsausgaenge der Strombegrenzer U5 und U9 (LOW = Stoerung). IO6: 24 V vorhanden (LOW = vorhanden), IO7: 5 V vorhanden (HIGH = vorhanden).
Leuchten auf der Platine
Anschluesse fuer Leuchten im Gehaeuse
Leuchtdioden ohne eingebauten Vorwiderstand; FAIL mit gemeinsamer Anode (gemeinsamer Pluspol). Seit 03.11.2026 schaltet je Ader eine Konstantstromsenke (Abschnitt 'Schutz gegen 24 V' unten): U8 LOW -> PNP Q13-Q16 -> NPN Q17-Q20 mit 300 Ohm im Emitter (etwa 8 mA), 24 V auf der Ader schadet nicht. J1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
J14: 1 = Plus beider Leuchten (Anoden), 2 = Rot, 3 = Gruen, 4 = Blau (FAIL), 5 = BEREIT
Schutz gegen 24 V: Endschalter J7-J10 (D20-D31)
TVS SMF30A an der Klemme (leitet unter 30 V nicht), Pull-up ueber 1N4148WS (sperrt 24 V von +3V3 weg; HIGH etwa 2,7 V), 22 kOhm (R13-R16) und Klemmdiode an +3V3: bei 25,2 V auf der Ader 0,97 mA ueber 22 kOhm in +3V3, Eingang von U2 etwa 3,9 V (zulaessig 6 V). Filter 22 kOhm/4,7 nF = 0,10 ms wie vor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
